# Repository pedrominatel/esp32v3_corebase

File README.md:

# ESP32 Core Base (for ESP32 V3 development)

KiCAD projetct template for ESP32 V3 projects

## ESP32 Datasheet
## ESP32 Docs

ESP32 V3 Core base with integrated USB to serial converter

### TODO:

#### Add project template

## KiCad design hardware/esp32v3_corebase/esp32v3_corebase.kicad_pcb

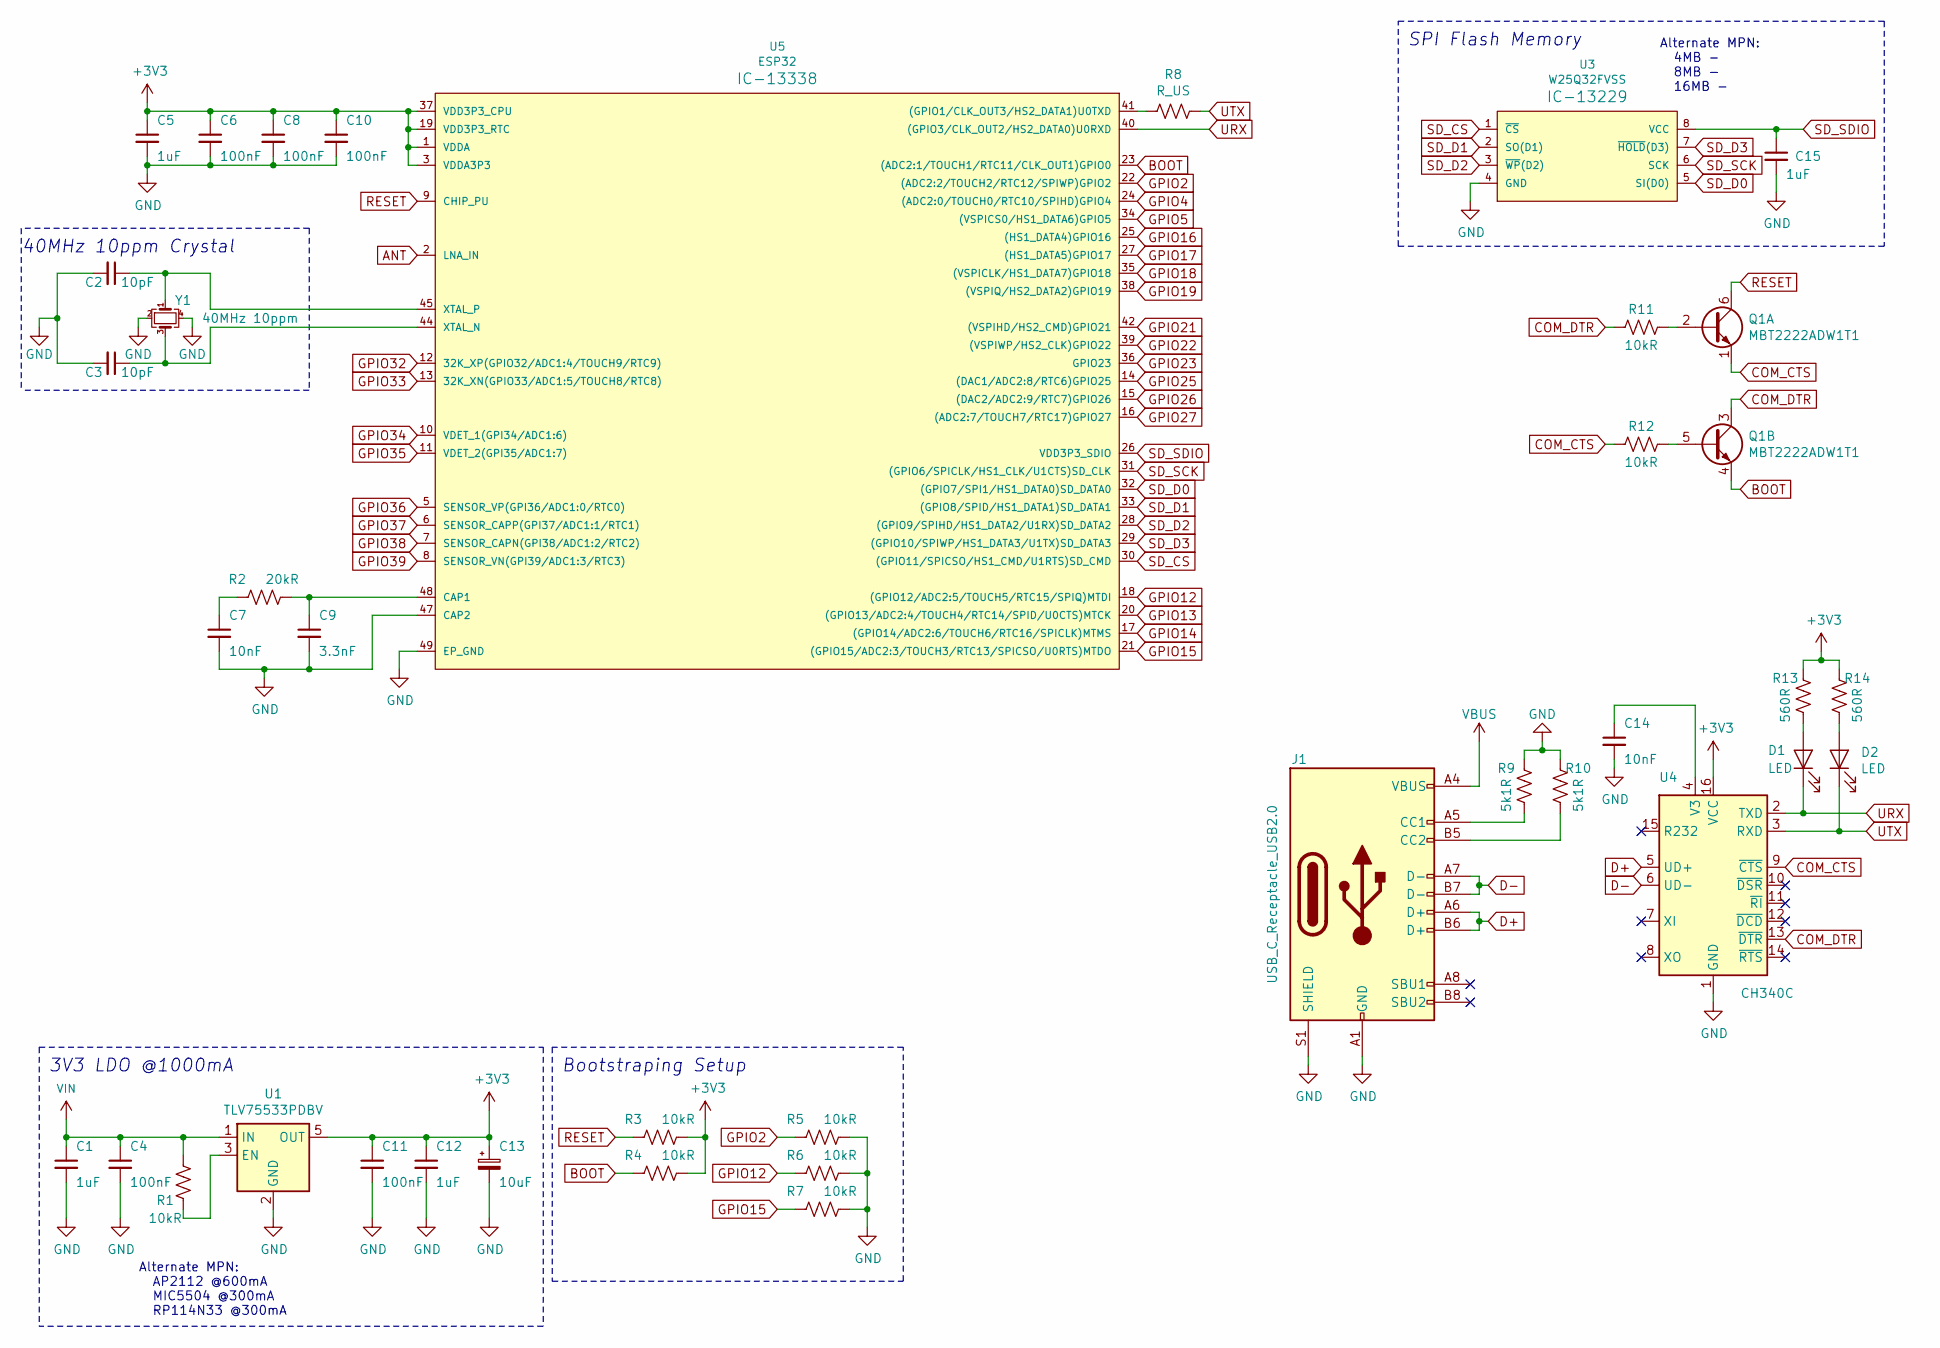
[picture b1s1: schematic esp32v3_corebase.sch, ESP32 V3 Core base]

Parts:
C1, C5, C12, C15: 1uF; 0603
C2, C3: 10pF; 0603
C4, C6, C8, C10, C11: 100nF; 0603
C7, C14: 10nF; 0603
C9: 3.3nF; 0603
C13: 10uF; 0603
D1, D2: LED; LED_0603_1608Metric
J1: USB_C_Receptacle_USB2.0; USB_C_Receptacle_Palconn_UTC16-G
Q1: MBT2222ADW1T1; SOT-363_SC-70-6
R1, R3, R4, R5, R6, R7, R11, R12: 10kR; 0603
R2: 20kR; 0603
R8: R_US; 0603
R9, R10: 5k1R; 0603
R13, R14: 560R; 0603
U1: TLV75533PDBV; SOT-23-5
U3: W25Q32FVSS; SOIC-8
U4: CH340C; SOIC-16_3.9x9.9mm_P1.27mm
U5: ESP32; QFN-48-1EP_6x6mm_P0.4mm_EP4.2x4.2mm
Y1: 40MHz 10ppm; CRYSTAL-SMD-3.2X2.5MM

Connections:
+3V3: C5.1, C6.1, C8.1, C10.1, C11.1, C12.1, C13.1, R3.1, R4.1, R13.2, R14.2, U1.5 (OUT), U4.16 (VCC), U5.1 (VDDA), U5.3 (VDDA3P3), U5.4 (VDDA3P3), U5.19 (VDD3P3_RTC), U5.37 (VDD3P3_CPU), U5.43 (VDDA), U5.46 (VDDA)
ANT: U5.2 (LNA_IN)
BOOT: Q1.4 (E2), R4.2, U5.23 ((ADC2:1/TOUCH1/RTC11/CLK_OUT1)GPIO0)
COM_CTS: Q1.1 (E1), R12.2, U4.9 (~CTS)
COM_DTR: Q1.3 (C2), R11.2, U4.13 (~DTR)
D+: J1.A6 (D+), J1.B6 (D+), U4.5 (UD+)
D-: J1.A7 (D-), J1.B7 (D-), U4.6 (UD-)
GND: C1.2, C2.2, C3.2, C4.2, C5.2, C6.2, C7.2, C8.2, C9.2, C10.2, C11.2, C12.2, C13.2, C14.2, C15.2, J1.A1 (GND), J1.A12 (GND), J1.B1 (GND), J1.B12 (GND), J1.S1 (SHIELD), R5.1, R6.1, R7.1, R9.2, R10.2, U1.2 (GND), U3.4 (GND), U4.1 (GND), U5.47 (CAP2), U5.49 (EP_GND), Y1.2, Y1.4
GPIO2: R5.2, U5.22 ((ADC2:2/TOUCH2/RTC12/SPIWP)GPIO2)
GPIO4: U5.24 ((ADC2:0/TOUCH0/RTC10/SPIHD)GPIO4)
GPIO5: U5.34 ((VSPICS0/HS1_DATA6)GPIO5)
GPIO12: R6.2, U5.18 ((GPIO12/ADC2:5/TOUCH5/RTC15/SPIQ)MTDI)
GPIO13: U5.20 ((GPIO13/ADC2:4/TOUCH4/RTC14/SPID/U0CTS)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)
GPIO14: U5.17 ((GPIO14/ADC2:6/TOUCH6/RTC16/SPICLK)MTMS)
GPIO15: R7.2, U5.21 ((GPIO15/ADC2:3/TOUCH3/RTC13/SPICSO/U0RT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)
GPIO16: U5.25 ((HS1_DATA4)GPIO16)
GPIO17: U5.27 ((HS1_DATA5)GPIO17)
GPIO18: U5.35 ((VSPICLK/HS1_DATA7)GPIO18)
GPIO19: U5.38 ((VSPIQ/HS2_DATA2)GPIO19)
GPIO21: U5.42 ((VSPIHD/HS2_CMD)GPIO21)
GPIO22: U5.39 ((VSPIWP/HS2_CLK)GPIO22)
GPIO23: U5.36 (GPIO23)
GPIO25: U5.14 ((DAC1/ADC2:8/RTC6)GPIO25)
GPIO26: U5.15 ((DAC2/ADC2:9/RTC7)GPIO26)
GPIO27: U5.16 ((ADC2:7/TOUCH7/RTC17)GPIO27)
GPIO32: U5.12 (32K_XP(GPIO32/ADC1:4/TOUCH9/RTC9))
GPIO33: U5.13 (32K_XN(GPIO33/ADC1:5/TOUCH8/RTC8))
GPIO34: U5.10 (VDET_1(GPI34/ADC1:6))
GPIO35: U5.11 (VDET_2(GPI35/ADC1:7))
GPIO36: U5.5 (SENSOR_VP(GPI36/ADC1:0/RTC0))
GPIO37: U5.6 (SENSOR_CAPP(GPI37/ADC1:1/RTC1))
GPIO38: U5.7 (SENSOR_CAPN(GPI38/ADC1:2/RTC2))
GPIO39: U5.8 (SENSOR_VN(GPI39/ADC1:3/RTC3))
unnamed: C2.1, U5.45 (XTAL_P), Y1.1
unnamed: C3.1, U5.44 (XTAL_N), Y1.3
unnamed: C7.1, R2.2
unnamed: C9.1, R2.1, U5.48 (CAP1)
unnamed: C14.1, U4.4 (V3)
unnamed: D1.2 (A), R13.1
unnamed: D2.2 (A), R14.1
unnamed: J1.A5 (CC1), R9.1
unnamed: J1.B5 (CC2), R10.1
unnamed: Q1.2 (B1), R11.1
unnamed: Q1.5 (B2), R12.1
unnamed: R1.1, U1.3 (EN)
unnamed: R8.2, U5.41 ((GPIO1/CLK_OUT3/HS2_DATA1)U0TXD)
RESET: Q1.6 (C1), R3.2, U5.9 (CHIP_PU)
SD_CS: U3.1 (~CS~), U5.30 ((GPIO11/SPICSO/HS1_CMD/U1RTS)SD_CMD)
SD_D0: U3.5 (SI(D0)), U5.32 ((GPIO7/SPI1/HS1_DATA0)SD_DATA0)
SD_D1: U3.2 (SO(D1)), U5.33 ((GPIO8/SPID/HS1_DATA1)SD_DATA1)
SD_D2: U3.3 (~WP~(D2)), U5.28 ((GPIO9/SPIHD/HS1_DATA2/U1RX)SD_DATA2)
SD_D3: U3.7 (~HOLD~(D3)), U5.29 ((GPIO10/SPIWP/HS1_DATA3/U1TX)SD_DATA3)
SD_SCK: U3.6 (SCK), U5.31 ((GPIO6/SPICLK/HS1_CLK/U1CTS)SD_CLK)
SD_SDIO: C15.1, U3.8 (VCC), U5.26 (VDD3P3_SDIO)
URX: D1.1 (K), U4.2 (TXD), U5.40 ((GPIO3/CLK_OUT2/HS2_DATA0)U0RXD)
UTX: D2.1 (K), R8.1, U4.3 (RXD)
VBUS: J1.A4 (VBUS), J1.A9 (VBUS), J1.B4 (VBUS), J1.B9 (VBUS)
VIN: C1.1, C4.1, R1.2, U1.1 (IN)

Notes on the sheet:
Alternate MPN: AP2112 @600mA MIC5504 @300mA RP114N33 @300mA
3V3 LDO @1000mA
Bootstraping Setup
SPI Flash Memory
Alternate MPN: 4MB - 8MB - 16MB -
40MHz 10ppm Crystal

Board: 2 copper layers, 38 parts (0 on the bottom side), 35 nets, no tracks yet.

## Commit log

2020-05-07 [FEATURE] Added ESP32, memory, LDO and bootstraping configuration
2020-05-11 [FEATURE] Added CH340C with USB type C connector
2020-05-17 [FEATURE] Changed resistors and capacitors footprint from 0603 to 0402
2020-05-25 [FEATURE] Minor changes on the circuit and VIN to 5V
2020-10-04 Added PSRAM and minor changes on sch
2020-10-04 Added schematic PDF
2020-10-04 Added 12MHz crystal for the CH340G version
